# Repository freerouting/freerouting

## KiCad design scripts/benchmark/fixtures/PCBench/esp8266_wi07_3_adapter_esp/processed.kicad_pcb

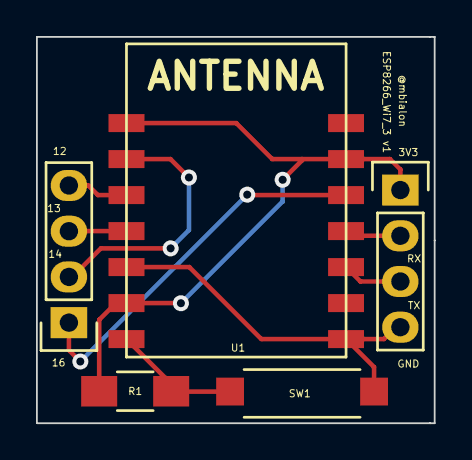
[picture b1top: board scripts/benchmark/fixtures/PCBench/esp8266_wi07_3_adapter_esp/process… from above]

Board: 2 copper layers, 22.1 x 21.5 mm, 5 parts (0 on the bottom side), 9 nets.

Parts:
P1, P2: CONN_01X04; Pin_Header_Straight_1x04
R1: 1k; R_1206_HandSoldering
SW1: SW_PUSH; SW_2
U1: ESP8266_Wi07-3; ESP8266_Wi07_3

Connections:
+3V3: P2.1, R1.1, U1.6, U1.8, U1.13
GND: P2.4, SW1.1, U1.1, U1.12
GPIO12: P1.4, U1.10
GPIO13: P1.3, U1.11
GPIO14: P1.2, U1.9
GPIO16: P1.1, U1.5
unnamed: R1.2, SW1.2, U1.14
RX: P2.2, U1.4
TX: P2.3, U1.3

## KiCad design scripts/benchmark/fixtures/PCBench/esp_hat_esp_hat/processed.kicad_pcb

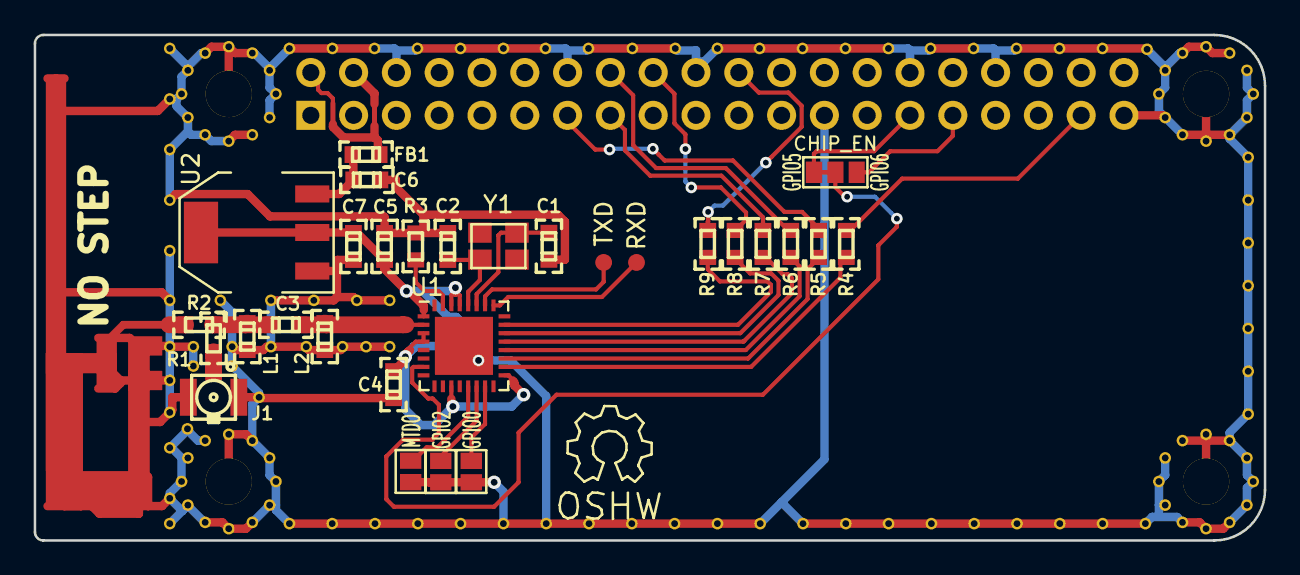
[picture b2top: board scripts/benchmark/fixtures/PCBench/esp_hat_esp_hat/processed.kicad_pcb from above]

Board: 2 copper layers, 73.0 x 30.0 mm, 35 parts (1 on the bottom side), 30 nets.

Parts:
ANT1: ANT_INVERTED_F; TI_DN007_2.4GHz
C1, C2: 10pF; 0603(1608m)-CHIP-CAP
C3: 5.6pF; 0603(1608m)-CHIP-CAP
C4, C5: 0.1uF; 0603(1608m)-CHIP-CAP
C6, C7: 10uF; 0603(1608m)-CHIP-CAP
FB1: FILTER; 0603(1608m)-CHIP-CAP
J1: DNP; U.FL-COAX
JP1: CHIP_EN; GS3
JP2: MTDO; GS2
JP3: GPIO2; GS2
JP4: GPIO0; GS2
L1, L2: DNP; 0603(1608m)-CHIP-CAP
P1: CONN_02X20; Socket_Strip_Straight_2x20_pi
R1: DNP; 0603(1608m)-CHIP-RESISTOR
R2: 0; 0603(1608m)-CHIP-RESISTOR
R3: 12.0K 1%; 0603(1608m)-CHIP-RESISTOR
R4, R5, R6, R7, R8, R9: 200; 0603(1608m)-CHIP-RESISTOR
U1: ESP8266EX; QFN-32-1EP_5x5mm_Pitch0.5mm
U2: AP1117D33; SOT-223-REG_VOUTSLUG
W1: RXD; Measurement_Point_Round-SMD-Pad_Small
W2: TXD; Measurement_Point_Round-SMD-Pad_Small
W3, W4, W5, W6: MOUNT; NPTH_Hole_2_75mm
Y1: 26MHz 10ppm; crystal_FA238-TSX3225

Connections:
+3V3: C4.1, C5.1, C7.1, U1.1, U1.3, U1.4, U1.11, U1.17, U1.29, U1.30, U2.2
+5V: FB1.1, P1.2, P1.4
/5V_filt: C6.1, FB1.2, U2.3
/50ohm_LNA: C3.1, L2.1, U1.2
/50ohm_ant: ANT1.2, R2.1
/50ohm_filt: C3.2, L1.1, R1.1, R2.2
/50ohm_ufl: J1.1, R1.2
GND: ANT1.1, C1.2, C2.2, C4.2, C5.2, C6.2, C7.2, J1.2, J1.3, JP2.2, JP3.2, JP4.2, L1.2, L2.2, P1.6, P1.14, P1.20, P1.25, P1.30, P1.34, P1.39, R3.1, U1.33, U2.1, W3.1, W4.1, W5.1, W6.1
GPIO5: JP1.1, JP1.2, P1.29, U1.7
GPIO6: JP1.3, P1.31
unnamed: C1.1, U1.27, Y1.1
unnamed: C2.1, U1.28, Y1.2
unnamed: JP2.1, U1.13
unnamed: JP3.1, U1.14
unnamed: JP4.1, U1.15
unnamed: R3.2, U1.31
unnamed: R4.2, U1.18
unnamed: R5.2, U1.19
unnamed: R6.2, U1.20
unnamed: R7.2, U1.21
unnamed: R8.2, U1.22
unnamed: R9.2, U1.23
unnamed: U1.25, W1.1
unnamed: U1.26, W2.1
SD_CLK: P1.15, R7.1
SD_CMD: P1.16, R6.1
SD_D0: P1.18, R8.1
SD_D1: P1.22, R9.1
SD_D2: P1.37, R4.1
SD_D3: P1.13, R5.1

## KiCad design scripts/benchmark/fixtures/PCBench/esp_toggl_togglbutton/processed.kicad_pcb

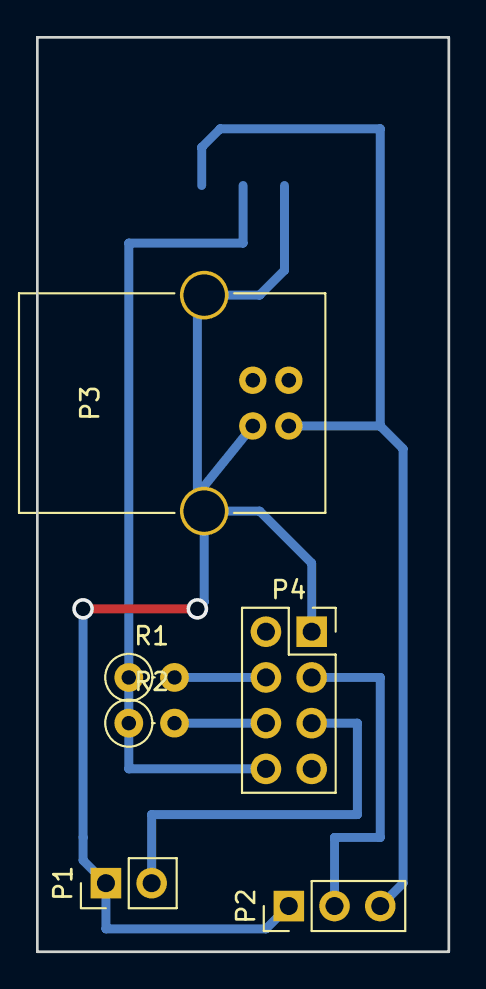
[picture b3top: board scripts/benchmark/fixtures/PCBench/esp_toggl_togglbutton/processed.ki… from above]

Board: 2 copper layers, 22.9 x 50.8 mm, 7 parts (1 on the bottom side), 7 nets.

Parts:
P1: Button; Pin_Header_Straight_1x02_Pitch2.54mm
P2: WS2812B; Pin_Header_Straight_1x03_Pitch2.54mm
P3: USB_B
P4: CONN_02X04; Socket_Strip_Straight_2x04_Pitch2.54mm
R1, R2: 10k; R_Axial_DIN0207_L6.3mm_D2.5mm_P2.54mm_Vertical
U1: NCP1117ST33T3G; SOT-223

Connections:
+5V: P2.3, P3.1, U1.3
GND: P1.1, P2.1, P3.4, P3.5, P4.1, U1.1
unnamed: P1.2, P4.5
unnamed: P2.2, P4.3
unnamed: P4.4, R1.2
unnamed: P4.6, R2.2
unnamed: P4.8, R1.1, R2.1, U1.2
